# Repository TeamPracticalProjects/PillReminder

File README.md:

# PillReminder
##A collaborative project by [Team Practical Projects](https://github.com/TeamPracticalProjects)

##What is the Pill Reminder?

As a person ages, we all know, it becomes more difficult to remember to take your pills. At some point a person is capable of living independently, but may not remember the current day of the week, or even what time of day. This can lead to a person taking more pills than they should, or to skipping a set of pills. The Pill Reminder is meant to be used by a person in this situation.

The assembled Pill Reminder project has 14 pill cups; one for AM and one for PM, all seven days of the week. Each pill cup has an LED associated with it. The LEDs are controlled by an Arduino processor. Only one LED is ever lit at a time. The Arduino keeps track of date and time so that the correct LED is on between 6am and noon, and another between 6pm and midnight. Our hope is that the user can be easily trained to only take pills when one of the LEDs is lit up. The LED that is on will tell them which pill cup to empty; if that cup is already empty, then they should not take more pills.

The care giver is responsible for assuring the correct operation of the Pill Reminder and for loading the pill cups as appropriate.

##How do you buy a Pill Reminder?

You can't buy one. The Pill Reminder is a do-it-yourself project. All the information you need to buy the parts and assemble you own Pill Reminder can be downloaded from this site - and it's free for non-commercial use!

##The History

The Pill Reminder is a project that came about through a conversation at a Baby Boomer Makers meet-up held at the Mid Peninsula TechShop (www.techshop.ws) one cold winter evening in 2013. Bob Glicksman had the idea for the Pill Reminder and said he always wanted to make one, but he could not find the right case. Jim Schrempp had been looking for a project and said, “if you make two of the electronics I'll make two of the cases.” That night the collaboration was born.

Bob and Jim agreed to make the project and release the plans as an open source project freely licensed for non-commercial use. As a user of these open source plans you make make one, or several, for you own use but you cannot make them to sell. If you modify the plans or kits in some way you are obligated to publish your modifications and to also license your modified plans under the same terms. Your modified plans must contain attribution back to Bob Glicksman and Jim Schrempp.

Since we built this project, there have been a number of sophisticated smart phone apps released to help with medication compliance. They are not suitable for someone who doesn't actively use a smart phone. Some of them have surprisingly good features. Jim did some research and wrote an article on the criteria he used and ends with a recommendation of [the best pill reminder app](https://www.techenhancedlife.com/citizen-research/best-pill-reminder-app-explorer-choice).

We hope you enjoy the project!  
Jim Schrempp and Bob Glicksman  
San Francisco Bay Area  
February 2014

Here's a [video of an early version](https://www.youtube.com/watch?v=8NOZzQJS1Nk) of the Pill Reminder.

Tags: pill reminder, drug reminder, prescription reminder, free, open source

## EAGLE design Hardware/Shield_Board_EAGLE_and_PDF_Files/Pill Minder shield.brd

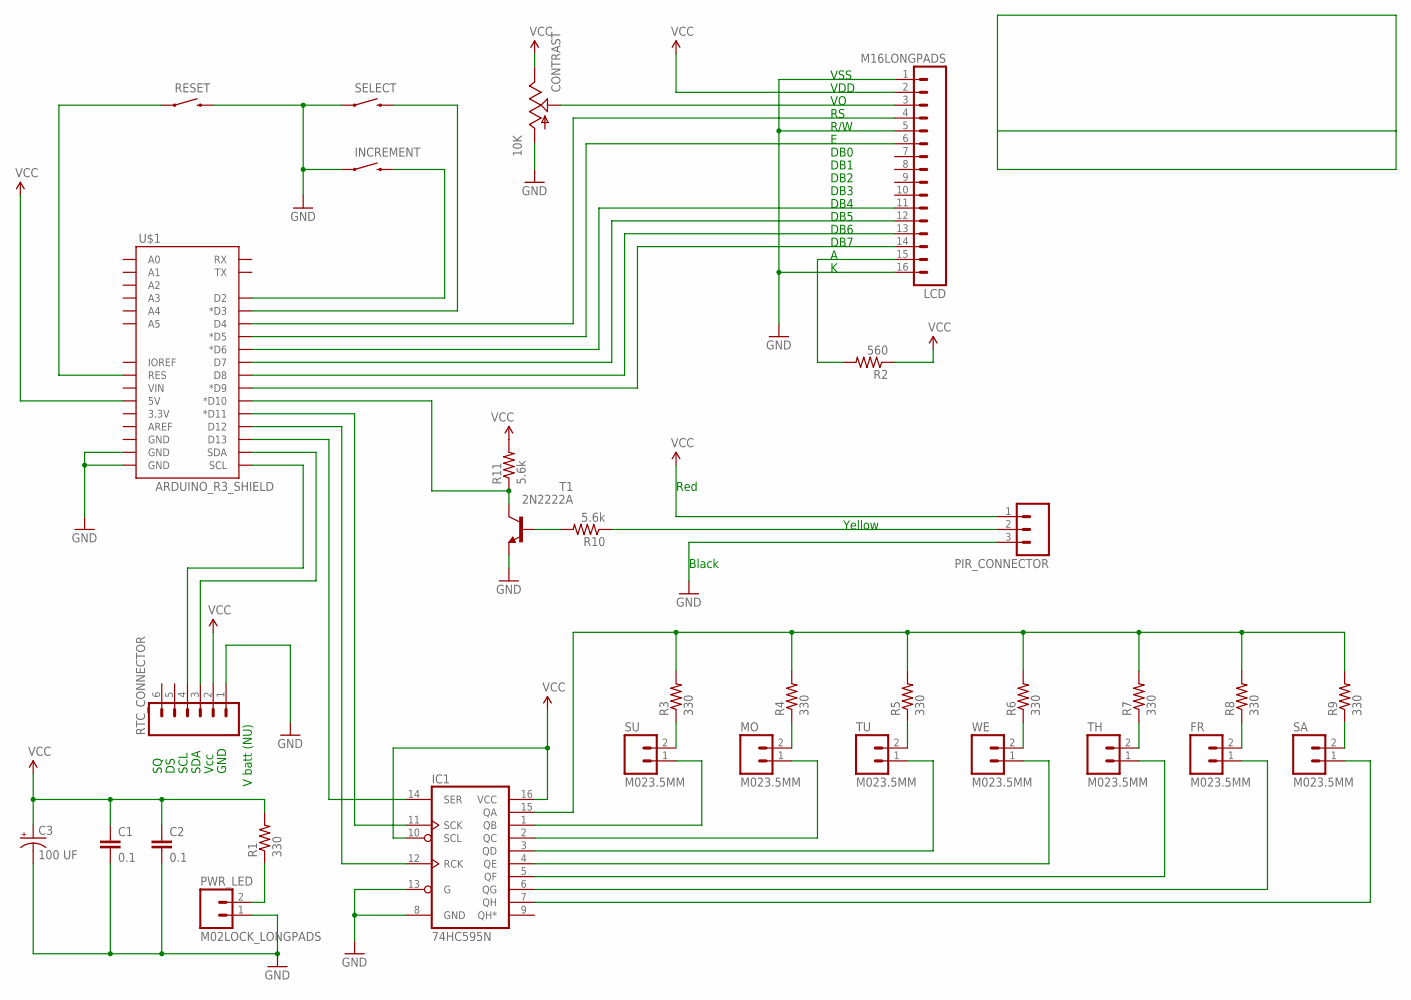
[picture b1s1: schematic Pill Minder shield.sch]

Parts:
C1, C2: 0.1; CAP-PTH-SMALL2
C3: 100 UF; CPOL-RADIAL-100UF-25V
CONTRAST: 10K; TRIM_POT
FR: M023.5MM; SCREWTERMINAL-3.5MM-2
IC1: 74HC595N; DIL16
INCREMENT: SWITCH-MOMENTARY-2PTH; TACTILE-PTH
LCD: M16LONGPADS; 1X16_LONGPADS
MO: M023.5MM; SCREWTERMINAL-3.5MM-2
PIR_CONNECTOR: M03LONGPADS; 1X03_LONGPADS
PWR_LED: M02LOCK_LONGPADS; 1X02_LOCK_LONGPADS
R1, R3, R4, R5, R6, R7, R8, R9: 330; AXIAL-0.4
R2: 560; AXIAL-0.4
R10, R11: 5.6k; AXIAL-0.4
RESET: SWITCH-MOMENTARY-2PTH; TACTILE-PTH
RTC_CONNECTOR: M06LONGPADS; 1X06_LONGPADS
SA: M023.5MM; SCREWTERMINAL-3.5MM-2
SELECT: SWITCH-MOMENTARY-2PTH; TACTILE-PTH
SU: M023.5MM; SCREWTERMINAL-3.5MM-2
T1: 2N2222A; TO92-EBC
TH: M023.5MM; SCREWTERMINAL-3.5MM-2
TU: M023.5MM; SCREWTERMINAL-3.5MM-2
U$1: ARDUINO_R3_SHIELD; UNO_R3_SHIELD
WE: M023.5MM; SCREWTERMINAL-3.5MM-2

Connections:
GND: C1.2, C2.2, C3.2 (-), CONTRAST.3 (A), IC1.8 (GND), IC1.13 (G), INCREMENT.1, LCD.1, LCD.5, LCD.16, PIR_CONNECTOR.3, PWR_LED.1, RESET.3 (2), RTC_CONNECTOR.1, SELECT.1, T1.E, U$1.GND@0 (GND), U$1.GND@1 (GND)
unnamed: RESET.1, U$1.RES
unnamed: IC1.7 (QH), SA.1
unnamed: IC1.1 (QB), SU.1
unnamed: R10.P$2 (2), T1.B
unnamed: IC1.2 (QC), MO.1
unnamed: IC1.3 (QD), TU.1
unnamed: IC1.4 (QE), WE.1
unnamed: IC1.5 (QF), TH.1
unnamed: FR.1, IC1.6 (QG)
unnamed: CONTRAST.1 (S), LCD.3
unnamed: SELECT.3 (2), U$1.D3 (*D3)
unnamed: INCREMENT.3 (2), U$1.D2
unnamed: IC1.14 (SER), U$1.D13
unnamed: IC1.12 (RCK), U$1.D12
unnamed: IC1.11 (SCK), U$1.D11 (*D11)
unnamed: RTC_CONNECTOR.4, U$1.SCL
unnamed: RTC_CONNECTOR.3, U$1.SDA
unnamed: LCD.4, U$1.D4
unnamed: LCD.6, U$1.D5 (*D5)
unnamed: LCD.11, U$1.D6 (*D6)
unnamed: LCD.12, U$1.D7
unnamed: LCD.13, U$1.D8
unnamed: LCD.14, U$1.D9 (*D9)
unnamed: LCD.15, R2.P$2 (2)
unnamed: R11.P$1 (1), T1.C, U$1.D10 (*D10)
unnamed: PWR_LED.2, R1.P$1 (1)
unnamed: PIR_CONNECTOR.2, R10.P$1 (1)
unnamed: R3.P$1 (1), SU.2
unnamed: MO.2, R4.P$1 (1)
unnamed: R5.P$1 (1), TU.2
unnamed: R6.P$1 (1), WE.2
unnamed: R7.P$1 (1), TH.2
unnamed: IC1.15 (QA), R3.P$2 (2), R4.P$2 (2), R5.P$2 (2), R6.P$2 (2), R7.P$2 (2), R8.P$2 (2), R9.P$2 (2)
unnamed: R9.P$1 (1), SA.2
unnamed: FR.2, R8.P$1 (1)
VCC: C1.1, C2.1, C3.1 (+), CONTRAST.2 (E), IC1.10 (SCL), IC1.16 (VCC), LCD.2, PIR_CONNECTOR.1, R1.P$2 (2), R2.P$1 (1), R11.P$2 (2), RTC_CONNECTOR.2, U$1.5V

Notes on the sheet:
V batt (NU)
GND
Vcc
SDA
SCL
VSS
VDD
R/W
DB0
DB1
DB2
DB3
DB4
DB5
DB6
DB7
Yellow
Black
Red

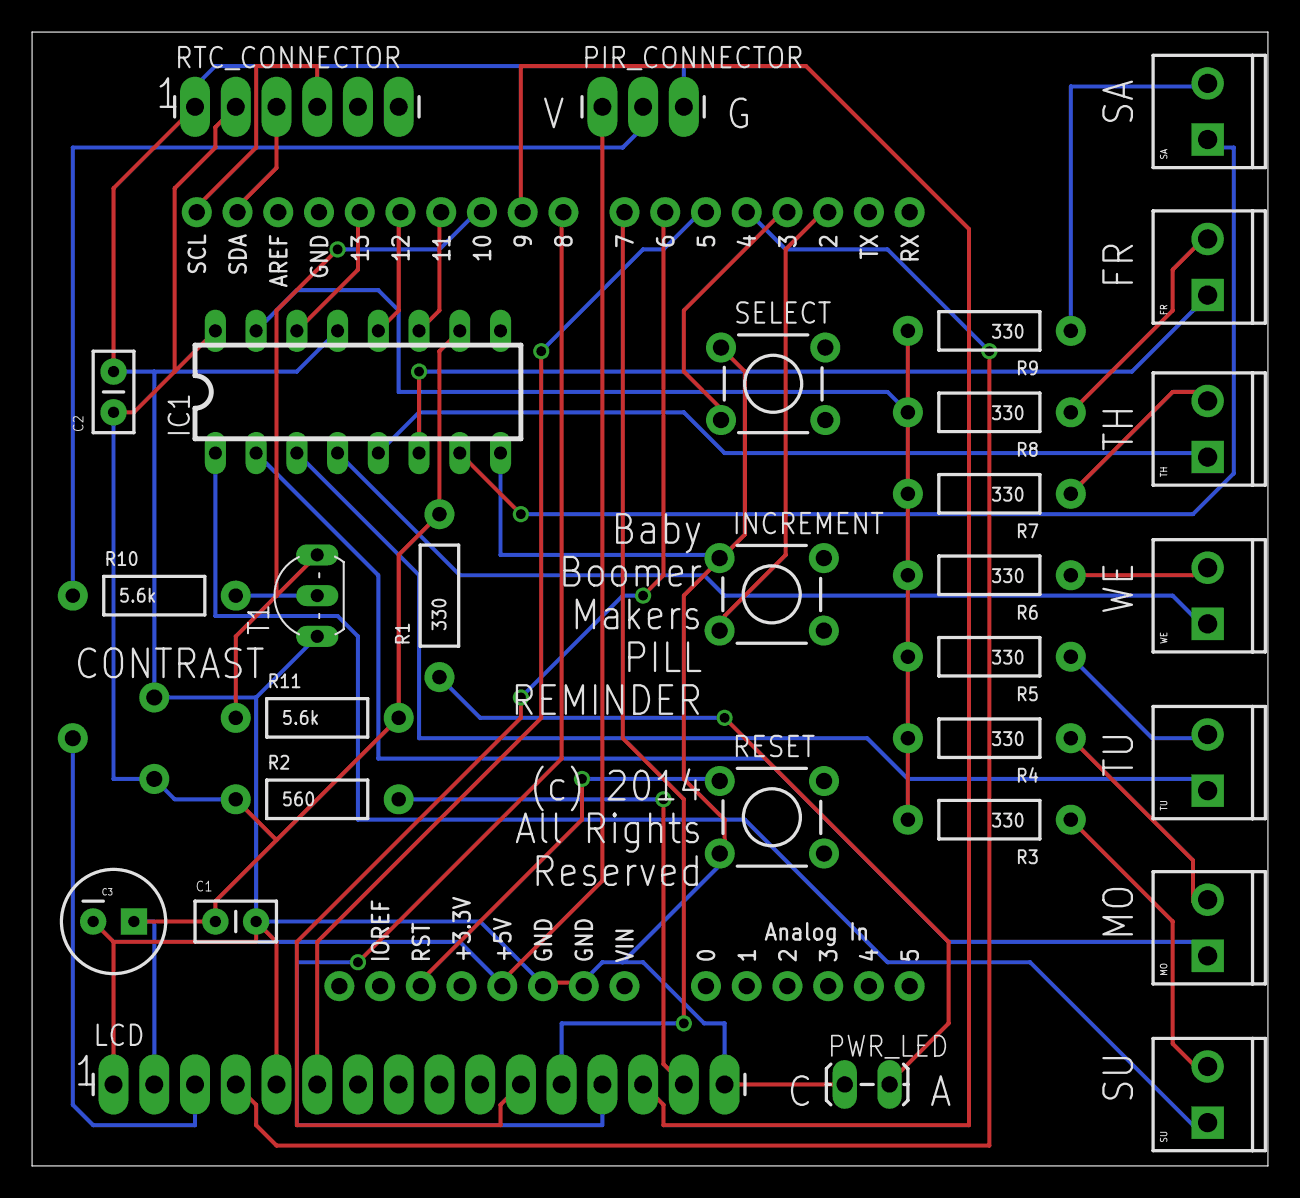
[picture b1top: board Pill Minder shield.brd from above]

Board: 2 copper layers, 77.1 x 70.7 mm, 32 parts (0 on the bottom side), 37 nets.

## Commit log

2015-11-14 Pill Reminder files from Shrimpware web site.
2016-11-29 Update README.md
    added a link to pill reminder app article on TEL.
2016-12-11 Update README.md
    Added a "tags" section to the bottom.
2017-04-30 removed old libraries
2017-04-30 added new libraries
2017-04-30 added a readme on the library update

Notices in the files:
Hardware/Shield_Board_EAGLE_and_PDF_Files/Pill Minder shield.brd:
(c) 2014
parts and their libraries:
SparkFun-DigitalIC: Licensing: CC v3.0 Share-Alike You are welcome to use this library for commercial purposes.
